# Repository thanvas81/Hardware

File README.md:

🚀 Embedded Systems & Electronics Design Portfolio

This repository is a collection of hardware, firmware, and PCB design projects I have built across the past year.
It is organized as a monorepo, where each folder represents a separate embedded-systems project, including Raspberry Pi HATs, sensor boards, analog filters, diagnostic tools, and custom control modules.

This portfolio is part of my application to the University of California, Berkeley, and showcases my experience in:

Embedded systems design

PCB layout & electronics hardware

Microcontroller programming

Signal processing

IoT sensors & digital interfaces

Electronics testing & validation

📁 Repository Structure

Each folder in this repository is a standalone hardware/firmware project.
Below is an index of the major projects:

📂 Full Project List

HAT_rpi/ – Raspberry Pi HAT with mixed-signal I/O.

bandpass_filter/ – Analog band-pass filter used for signal conditioning.

buzzer_door_detect_board/ – Door detection + buzzer notification circuit.

can_bus_extension_v2/ – CAN bus expansion board.

canlink/ – CAN communication module.

control-unit-v2-upper/ – Upper control unit for embedded system integration.

control_unit_tester/ – Bench-top electronics diagnostic/testing tool.

ds18b20_protection/ – Protection adapter for DS18B20 temperature sensors.

dummy_control_unit/ – Mock control unit for lab testing.

led-display/ – Custom LED display driver board.

lightsensor/ – Light-sensing analog front-end.

mini_upper_board_relay_analog/ – Compact control/relay board.

rfid_rpi_hat/ – RFID HAT for Raspberry Pi.

rgb_led/ – RGB LED driver circuit.

rpi-pico-diagnostic-tester/ – RP2040-based I/O diagnostic and logic-level tester.

serial_io_expander/ – Serial digital I/O expansion board.

switches_board/ – Switch interface board.

test/ – Miscellaneous test files.

tracker-master/ – Tracking/monitoring module.

upper-board-analog-inputs-and-relay/ – Analog input + relay control upper board.

upperboard_analog_relay_input/ – Relay + analog input interface board.

vehicle_io_validator/ – Automotive I/O validator.

(You can edit the descriptions later if you want more detail.)

🛠️ Technologies & Tools

Hardware Design

PCB design tools (KiCad)

Analog & digital circuit design

Embedded hardware validation

CAN, I2C, SPI, UART interfaces

C microcontroller firmware

Python (Raspberry Pi, testing scripts)

RP2040 (Raspberry Pi Pico)

Raspberry Pi OS

Testing Equipment

Oscilloscope

Logic analyzer

Multimeter & bench power supplies

📘 How to Explore

Each project folder may contain:

Schematics

PCB layouts

Documentation

You can browse any project individually by opening its folder.

🎯 Purpose of This Repository

This monorepo serves as a technical portfolio demonstrating my practical experience with embedded systems, electronics engineering, and real-world hardware development.
I hope it provides a clear view of my engineering interests and capabilities.

📬 Contact

If you have any questions or want to discuss these projects, feel free to reach out:

Athanasios Vasiloglou
th.vasiloglou81@gmail.com

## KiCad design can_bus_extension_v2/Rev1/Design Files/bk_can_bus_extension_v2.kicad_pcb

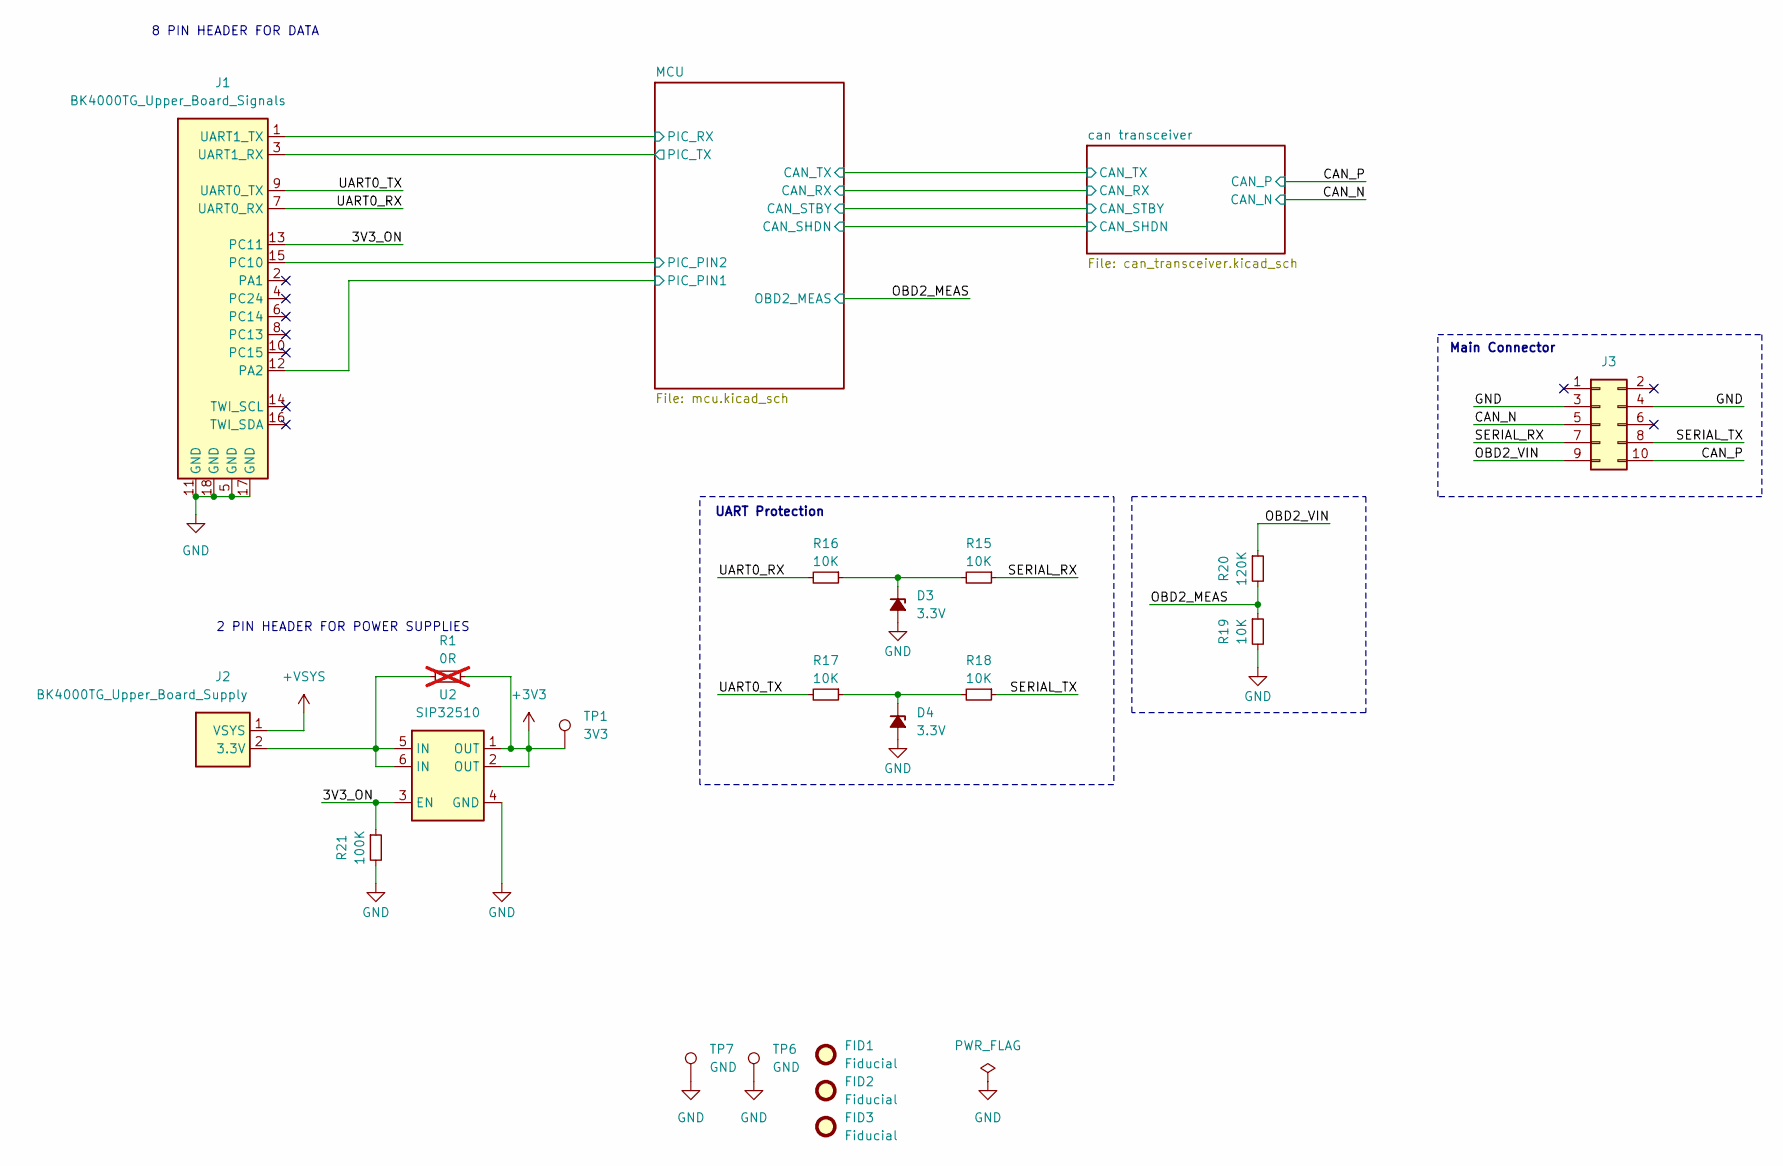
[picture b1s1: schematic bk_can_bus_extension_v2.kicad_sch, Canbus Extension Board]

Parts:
D3, D4: 3.3V; D_SOD-123
FID1, FID2, FID3: Fiducial; Fiducial_1mm_Mask2mm
J1: BK4000TG_Upper_Board_Signals; PinSocket_2x09_P2.54mm_Vertical
J2: BK4000TG_Upper_Board_Supply; PinSocket_1x02_P2.54mm_Vertical
J3: Conn_02x05_Odd_Even; Molex_Mini-Fit_Jr_5569-10A2_2x05_P4.20mm_Horizontal
R1: 0R; R_0805_2012Metric_Pad1.20x1.40mm_HandSolder; not fitted
R15, R16, R17, R18, R19: 10K; R_0603_1608Metric
R20: 120K; R_0603_1608Metric
R21: 100K; R_0603_1608Metric
TP1: 3V3; TestPoint_Pad_D2.0mm
TP6, TP7: GND; TestPoint_Pad_D2.0mm
U2: SIP32510; TSOT-23-6

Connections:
+3V3: R1.2, TP1.1, U2.1 (OUT), U2.2 (OUT); also elsewhere on the board
+VSYS: J2.1 (VSYS)
/3V3_ON: J1.13 (PC11), R21.1, U2.3 (EN)
/CAN_N: J3.5; also elsewhere on the board
/CAN_P: J3.10; also elsewhere on the board
/MCU/PIC_PIN1: J1.12 (PA2); also elsewhere on the board
/MCU/PIC_PIN2: J1.15 (PC10); also elsewhere on the board
/MCU/PIC_RX: J1.1 (UART1_TX); also elsewhere on the board
/MCU/PIC_TX: J1.3 (UART1_RX); also elsewhere on the board
/OBD2_MEAS: R19.1, R20.2; also elsewhere on the board
/OBD2_VIN: J3.9, R20.1
/SERIAL_RX: J3.7, R15.1
/SERIAL_TX: J3.8, R18.1
/UART0_RX: J1.7 (UART0_RX), R16.2
/UART0_TX: J1.9 (UART0_TX), R17.2
GND: D3.2 (A), D4.2 (A), J1.5 (GND), J1.11 (GND), J1.17 (GND), J1.18 (GND), J3.3, J3.4, R19.2, R21.2, TP6.1, TP7.1, U2.4 (GND); also elsewhere on the board
unnamed: D3.1 (K), R15.2, R16.1
unnamed: D4.1 (K), R17.1, R18.2
unnamed: J2.2 (3.3V), R1.1, U2.5 (IN), U2.6 (IN)

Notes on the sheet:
8 PIN HEADER FOR DATA
2 PIN HEADER FOR POWER SUPPLIES
Main Connector
UART Protection

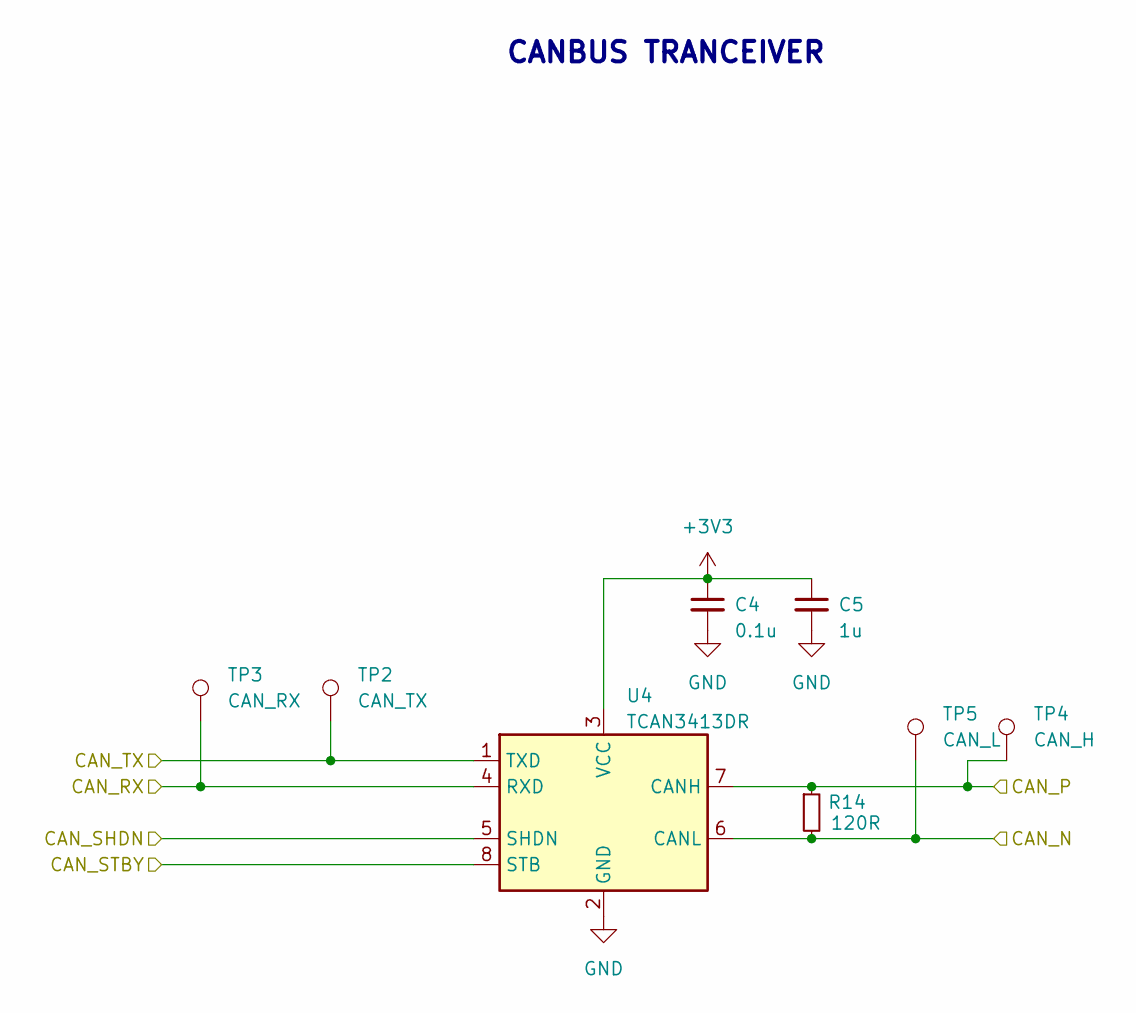
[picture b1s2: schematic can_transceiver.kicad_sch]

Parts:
C4: 0.1u; C_0603_1608Metric
C5: 1u; C_0603_1608Metric
R14: 120R; R_0805_2012Metric
TP2: CAN_TX; TestPoint_Pad_D2.0mm
TP3: CAN_RX; TestPoint_Pad_D2.0mm
TP4: CAN_H; TestPoint_Pad_D2.0mm
TP5: CAN_L; TestPoint_Pad_D2.0mm
U4: TCAN3413DR; SOIC-8_3.9x4.9mm_P1.27mm

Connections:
+3V3: C4.1, C5.1, U4.3 (VCC); also elsewhere on the board
/CAN_N: R14.2, TP5.1, U4.6 (CANL); also elsewhere on the board
/CAN_P: R14.1, TP4.1, U4.7 (CANH); also elsewhere on the board
/MCU/CAN_RX: TP3.1, U4.4 (RXD); also elsewhere on the board
/MCU/CAN_SHDN: U4.5 (SHDN); also elsewhere on the board
/MCU/CAN_STBY: U4.8 (STB); also elsewhere on the board
/MCU/CAN_TX: TP2.1, U4.1 (TXD); also elsewhere on the board
GND: C4.2, C5.2, U4.2 (GND); also elsewhere on the board

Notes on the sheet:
CANBUS TRANCEIVER

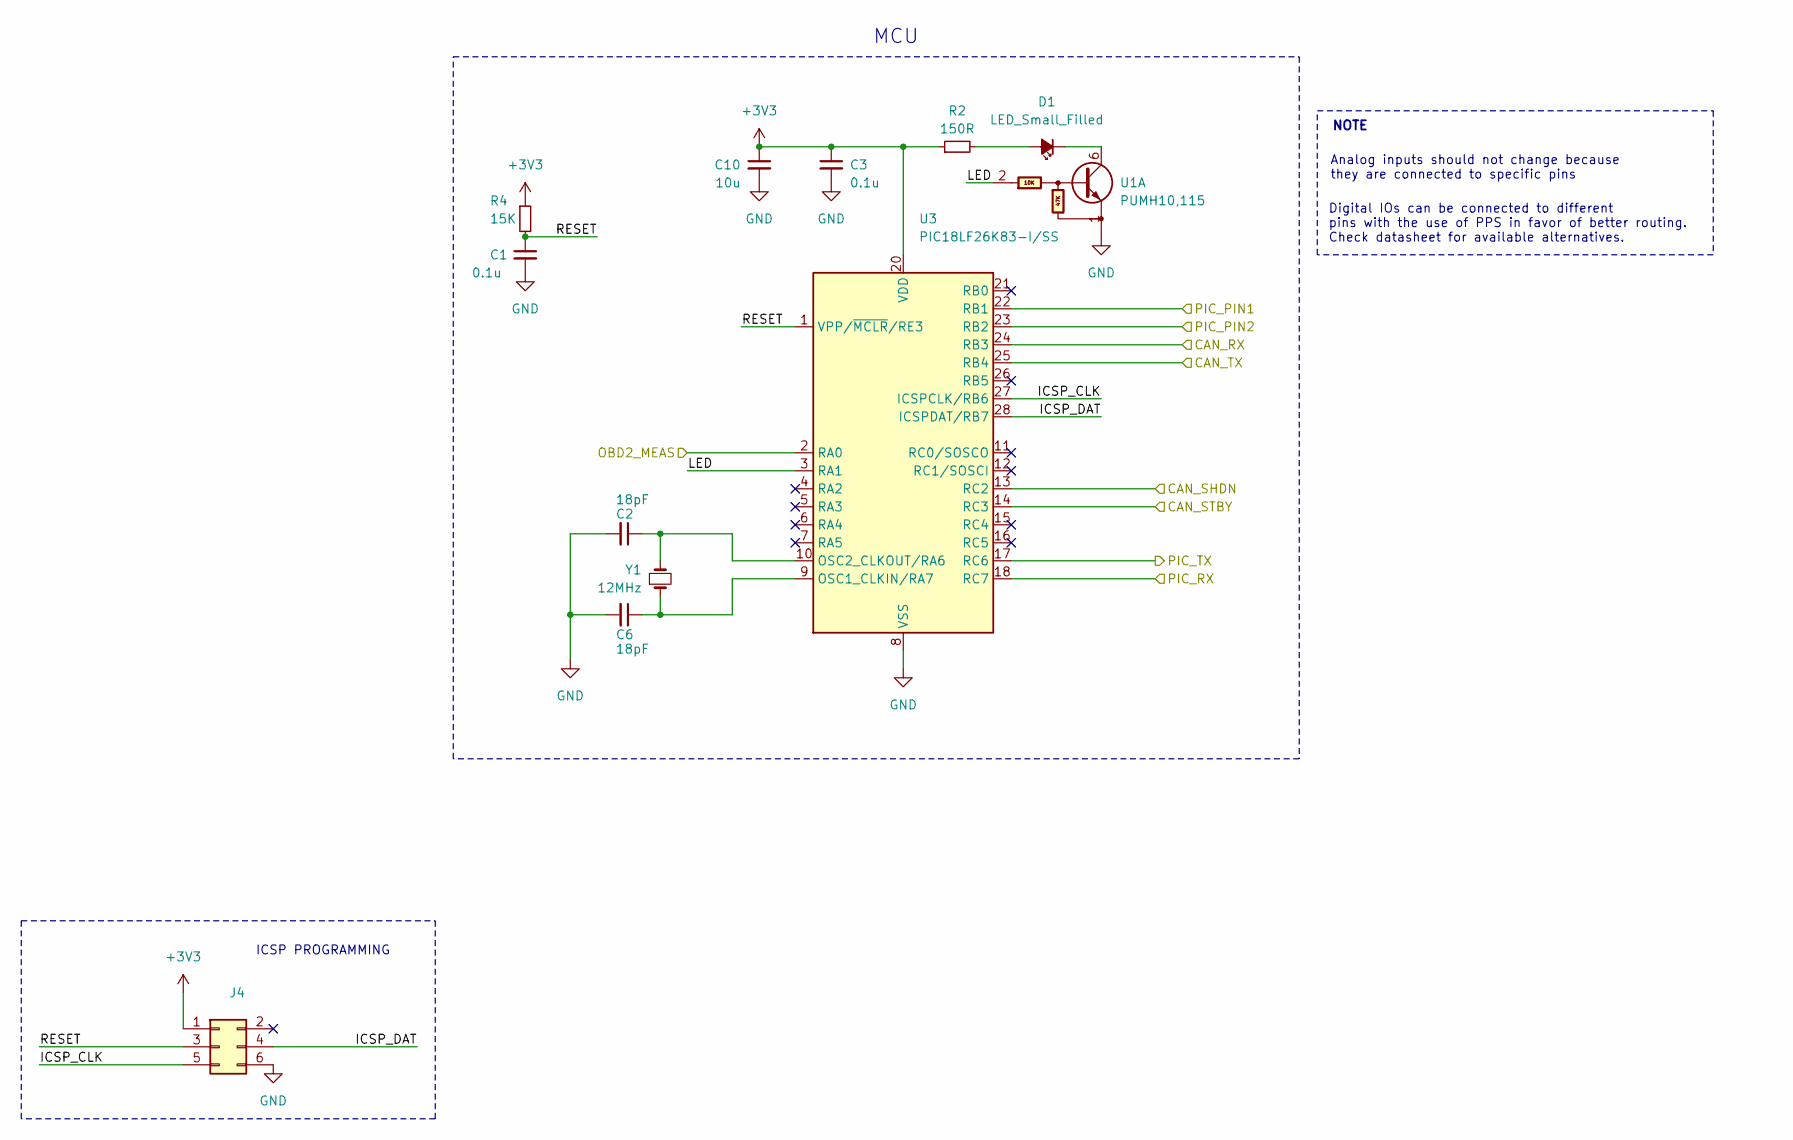
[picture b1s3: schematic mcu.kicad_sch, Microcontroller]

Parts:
C1, C3: 0.1u; C_0603_1608Metric
C2, C6: 18pF; C_0603_1608Metric
C10: 10u; C_0805_2012Metric
D1: LED_Small_Filled; LED_0603_1608Metric
J4: -; PinHeader_2x03_P2.54mm_Vertical
R2: 150R; R_0603_1608Metric
R4: 15K; R_0603_1608Metric
U1: PUMH10,115; SOT-363_SC-70-6
U3: PIC18LF26K83-I/SS; SSOP-28_5.3x10.2mm_P0.65mm
Y1: 12MHz; Crystal_SMD_5032-2Pin_5.0x3.2mm

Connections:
+3V3: C3.1, C10.1, J4.1, R2.1, R4.1, U3.20 (VDD); also elsewhere on the board
/MCU/CAN_RX: U3.24 (RB3); also elsewhere on the board
/MCU/CAN_SHDN: U3.13 (RC2); also elsewhere on the board
/MCU/CAN_STBY: U3.14 (RC3); also elsewhere on the board
/MCU/CAN_TX: U3.25 (RB4); also elsewhere on the board
/MCU/ICSP_CLK: J4.5, U3.27 (ICSPCLK/RB6)
/MCU/ICSP_DAT: J4.4, U3.28 (ICSPDAT/RB7)
/MCU/LED: U1.2, U3.3 (RA1)
/MCU/PIC_PIN1: U3.22 (RB1); also elsewhere on the board
/MCU/PIC_PIN2: U3.23 (RB2); also elsewhere on the board
/MCU/PIC_RX: U3.18 (RC7); also elsewhere on the board
/MCU/PIC_TX: U3.17 (RC6); also elsewhere on the board
/MCU/RESET: C1.1, J4.3, R4.2, U3.1 (VPP/~MCLR/RE3)
/OBD2_MEAS: U3.2 (RA0); also elsewhere on the board
GND: C1.2, C2.2, C3.2, C6.2, C10.2, J4.6, U1.1, U3.8 (VSS), U3.19 (VSS); also elsewhere on the board
unnamed: D1.2 (A), R2.2
unnamed: D1.1 (K), U1.6
unnamed: C6.1, U3.9 (OSC1_CLKIN/RA7), Y1.1
unnamed: C2.1, U3.10 (OSC2_CLKOUT/RA6), Y1.2

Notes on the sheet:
Digital IOs can be connected to different pins with the use of PPS in favor of better routing. Check datasheet for available alternatives.
NOTE
MCU
Analog inputs should not change because they are connected to specific pins
ICSP PROGRAMMING

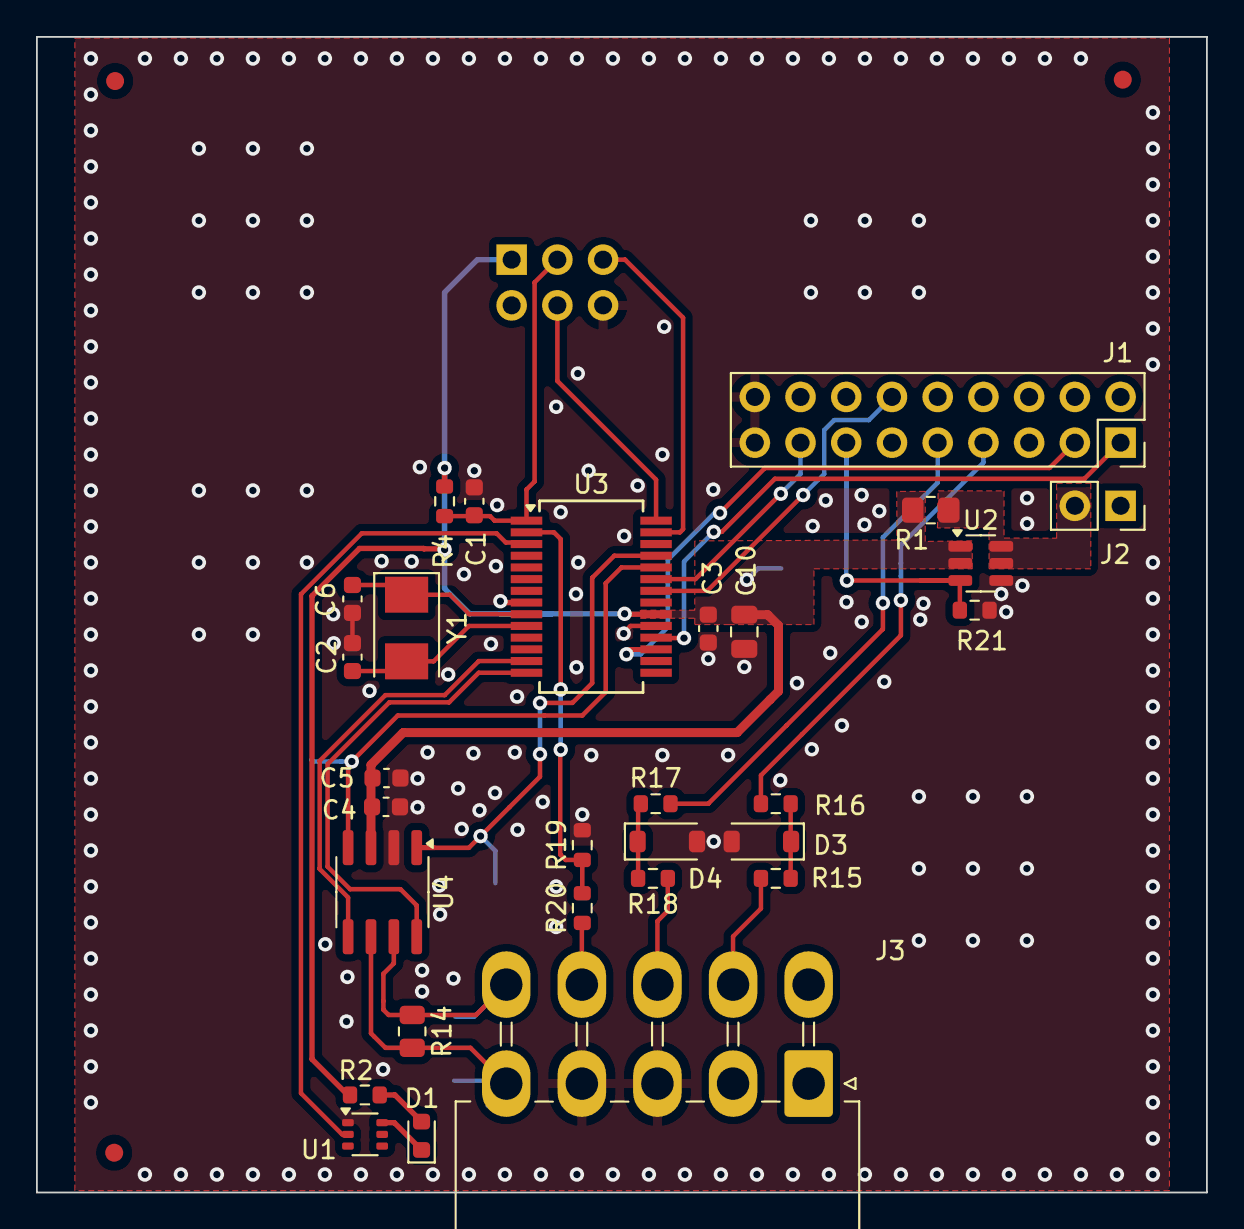
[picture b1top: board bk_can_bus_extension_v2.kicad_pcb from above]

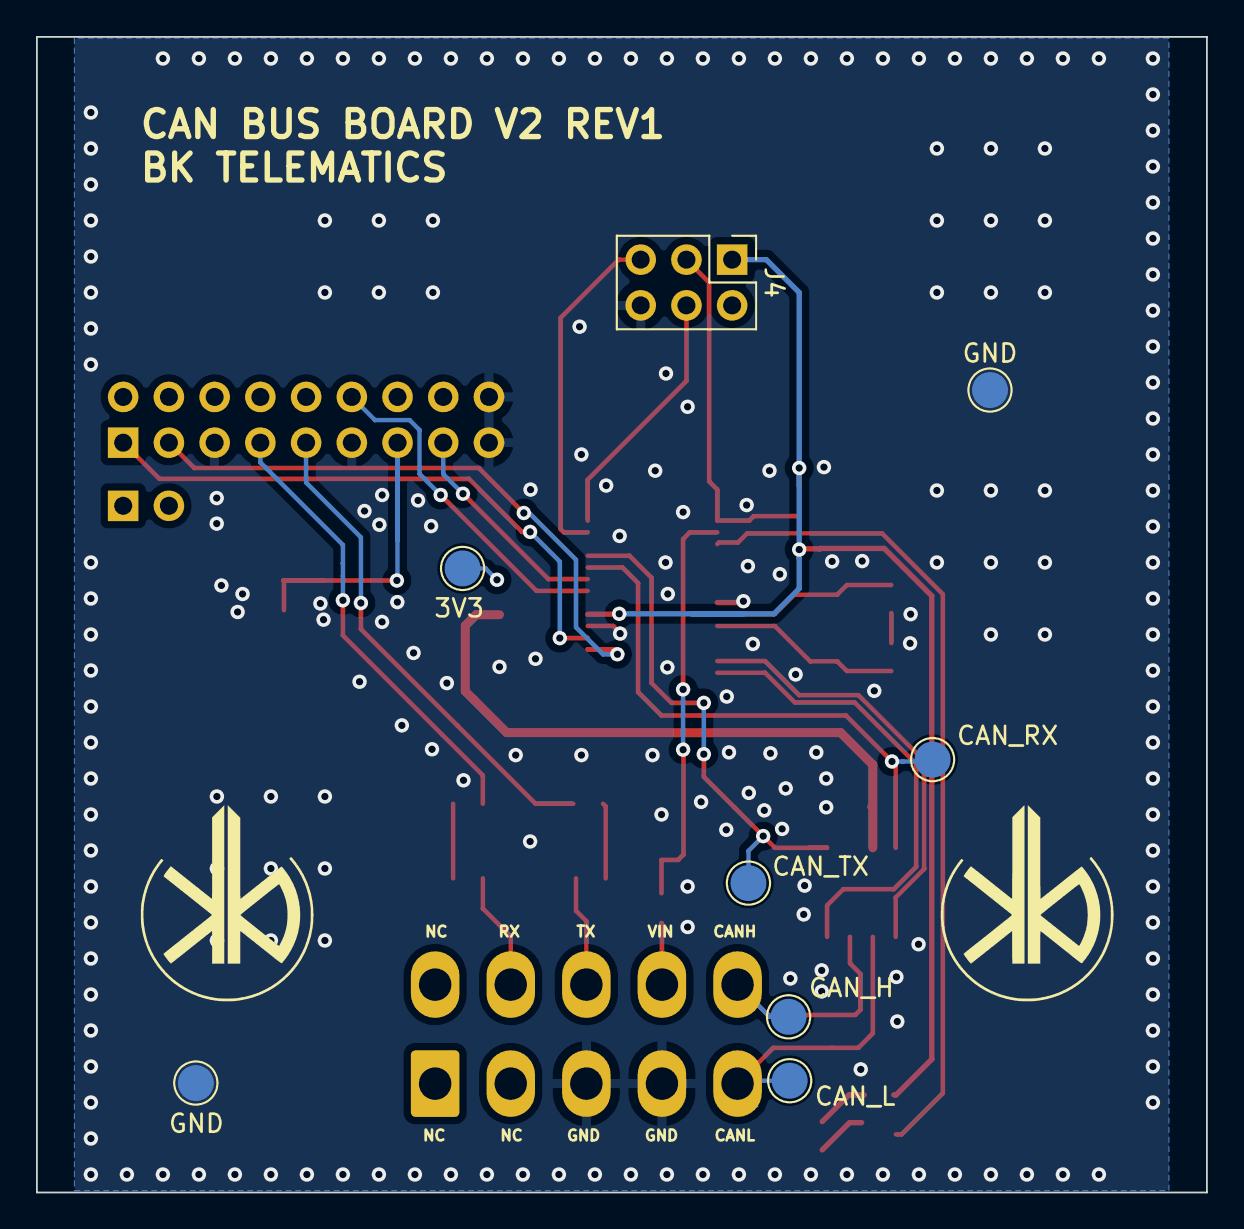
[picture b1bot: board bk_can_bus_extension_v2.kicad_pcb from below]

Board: 2 copper layers, 65.0 x 64.2 mm, 40 parts (8 on the bottom side), 30 nets.

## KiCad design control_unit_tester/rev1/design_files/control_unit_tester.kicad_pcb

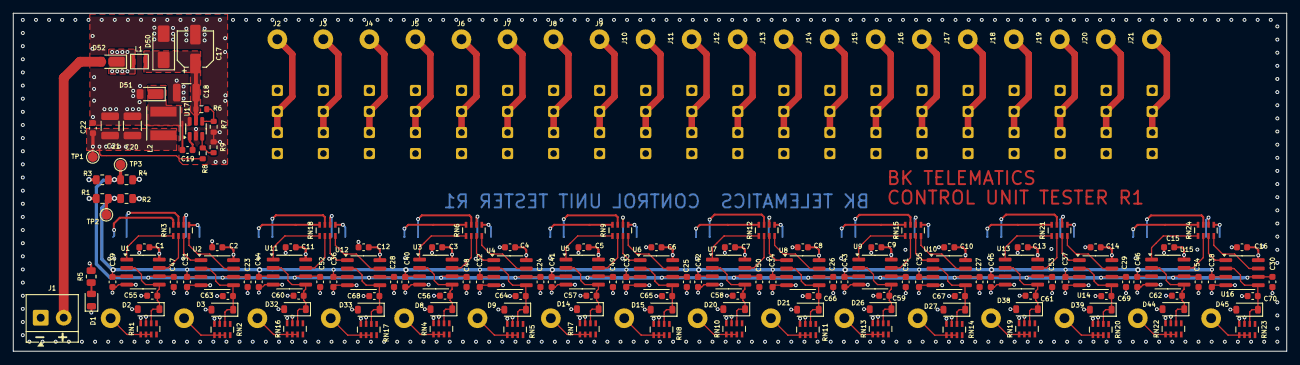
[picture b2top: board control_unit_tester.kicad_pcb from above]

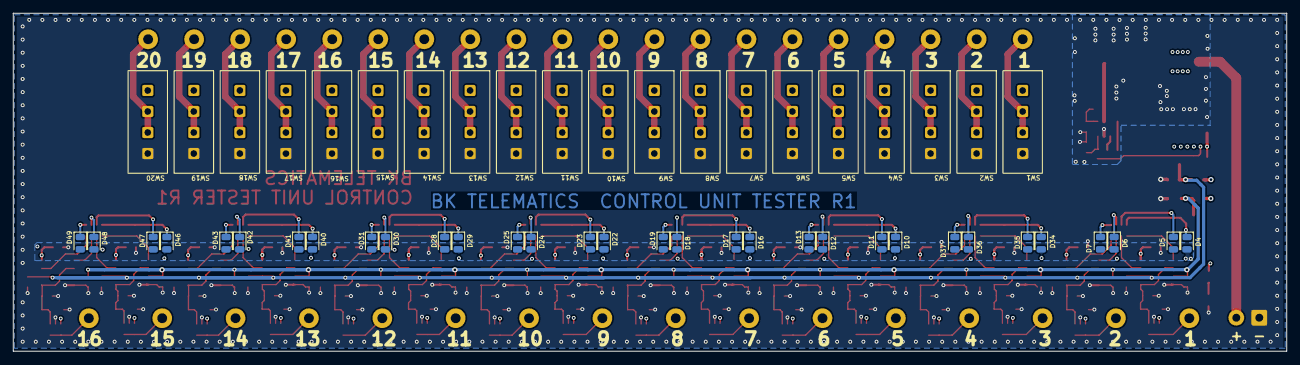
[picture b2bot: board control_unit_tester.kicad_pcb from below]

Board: 4 copper layers, 193.9 x 51.5 mm, 234 parts (52 on the bottom side), 128 nets.

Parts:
C1, C2, C3, C4, C5, C6, C7, C8, C9, C10, C11, C12, C13, C14, C15, C16, C19, C22, C23, C24, C25, C26, C27, C28, C29, C30, C31, C32, C33, C34, C35, C36, C37, C38, C39, C40, C41, C42, C43, C44, C45, C46, C47, C48, C49, C50, C51, C52, C53, C54, C55, C56, C57, C58, C59, C60, C61, C62, C63, C64, C65, C66, C67, C68, C69, C70: 0.1u; C_0603_1608Metric
C17: 10u; CP_Elec_5x5.3
C18: 2.2u; C_1210_3225Metric
C20, C21: 22u; C_1210_3225Metric
D1: LED 0805 SMD; LED_0805_2012Metric
D2, D3, D8, D9, D14, D15, D20, D21, D26, D27, D32, D33, D38, D39, D44, D45: 4.7V; D_SOD-123
D4, D5, D6, D7, D10, D11, D12, D13, D16, D17, D18, D19, D22, D23, D24, D25, D28, D29, D30, D31, D34, D35, D36, D37, D40, D41, D42, D43, D46, D47, D48, D49: LED; LED_0805_2012Metric
D50: SMAJ40CAe3/TR13; D_SMA
D51, D52: SBR3U60P1Q-7; D_PowerDI-123
J1: Conn_01x02; TerminalBlock_4Ucon_1x02_P3.50mm_Horizontal
J2, J3, J4, J5, J6, J7, J8, J9, J10, J11, J12, J13, J14, J15, J16, J17, J18, J19, J20, J21, J22, J23, J24, J25, J26, J27, J28, J29, J30, J31, J32, J33, J34, J35, J36, J37: T.H. Pad; Hole_pad_1.5x3_round
L1: 4.7uH; L_TDK_VLS252012HBX
L2: 22uH; L_Taiyo-Yuden_NR-50xx
R1, R4: 20Κ; R_0805_2012Metric
R2, R3: 80Κ; R_0805_2012Metric
R5: 470R; R_0805_2012Metric
R6, R7: 100K; R_0603_1608Metric
R8: 54.9K; R_0603_1608Metric
R9: 10K; R_0603_1608Metric
RN1, RN2, RN4, RN5, RN7, RN8, RN10, RN11, RN13, RN14, RN16, RN17, RN19, RN20, RN22, RN23: 1K; R_Array_Concave_4x0603
RN3, RN6, RN9, RN12, RN15, RN18, RN21, RN24: 470R; R_Array_Concave_4x0603
SW1, SW2, SW3, SW4, SW5, SW6, SW7, SW8, SW9, SW10, SW11, SW12, SW13, SW14, SW15, SW16, SW17, SW18, SW19, SW20: SLW-156646-5A-N-D
TP1, TP2, TP3: TestPoint; TestPoint_Pad_D1.5mm
U1, U2, U3, U4, U5, U6, U7, U8, U9, U10, U11, U12, U13, U14, U15, U16: AZV3002S-13; SOIC-8_3.9x4.9mm_P1.27mm
U17: LV2862x; SOT-23-6

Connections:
+5V: C1.1, C2.1, C3.1, C4.1, C5.1, C6.1, C7.1, C8.1, C9.1, C10.1, C11.1, C12.1, C13.1, C14.1, C15.1, C16.1, C20.1, C21.1, C22.1, D4.2 (A), D5.2 (A), D6.2 (A), D7.2 (A), D10.2 (A), D11.2 (A), D12.2 (A), D13.2 (A), D16.2 (A), D17.2 (A), D18.2 (A), D19.2 (A), D22.2 (A), D23.2 (A), D24.2 (A), D25.2 (A), D28.2 (A), D29.2 (A), D30.2 (A), D31.2 (A), D34.2 (A), D35.2 (A), D36.2 (A), D37.2 (A), D40.2 (A), D41.2 (A), D42.2 (A), D43.2 (A), D46.2 (A), D47.2 (A), D48.2 (A), D49.2 (A), L2.2, R1.1, R3.1, R5.2, R8.2, RN1.8 (R1.2), RN2.4 (R4.1), RN4.8 (R1.2), RN5.4 (R4.1), RN7.8 (R1.2), RN8.4 (R4.1), RN10.8 (R1.2), RN11.4 (R4.1), RN13.8 (R1.2), RN14.4 (R4.1), RN16.8 (R1.2), RN17.4 (R4.1), RN19.8 (R1.2), RN20.4 (R4.1), RN22.8 (R1.2), RN23.4 (R4.1), TP1.1, U1.8 (V+), U2.8 (V+), U3.8 (V+), U4.8 (V+), U5.8 (V+), U6.8 (V+), U7.8 (V+), U8.8 (V+), U9.8 (V+), U10.8 (V+), U11.8 (V+), U12.8 (V+), U13.8 (V+), U14.8 (V+), U15.8 (V+), U16.8 (V+)
+VIN: D52.1 (K), L1.1, SW1.1, SW2.1, SW3.1, SW4.1, SW5.1, SW6.1, SW7.1, SW8.1, SW9.1, SW10.1, SW11.1, SW12.1, SW13.1, SW14.1, SW15.1, SW16.1, SW17.1, SW18.1, SW19.1, SW20.1
/IN1: J22.1, RN1.1 (R1.1), RN1.2 (R2.1), RN1.3 (R3.1)
/IN2: J23.1, RN2.5 (R4.2), RN2.6 (R3.2), RN2.7 (R2.2)
/IN3: J26.1, RN4.1 (R1.1), RN4.2 (R2.1), RN4.3 (R3.1)
/IN4: J27.1, RN5.5 (R4.2), RN5.6 (R3.2), RN5.7 (R2.2)
/IN5: J28.1, RN7.1 (R1.1), RN7.2 (R2.1), RN7.3 (R3.1)
/IN6: J29.1, RN8.5 (R4.2), RN8.6 (R3.2), RN8.7 (R2.2)
/IN7: J30.1, RN10.1 (R1.1), RN10.2 (R2.1), RN10.3 (R3.1)
/IN8: J31.1, RN11.5 (R4.2), RN11.6 (R3.2), RN11.7 (R2.2)
/IN9: J32.1, RN13.1 (R1.1), RN13.2 (R2.1), RN13.3 (R3.1)
/IN10: J33.1, RN14.5 (R4.2), RN14.6 (R3.2), RN14.7 (R2.2)
/IN11: J24.1, RN16.1 (R1.1), RN16.2 (R2.1), RN16.3 (R3.1)
/IN12: J25.1, RN17.5 (R4.2), RN17.6 (R3.2), RN17.7 (R2.2)
/IN13: J34.1, RN19.1 (R1.1), RN19.2 (R2.1), RN19.3 (R3.1)
/IN14: J35.1, RN20.5 (R4.2), RN20.6 (R3.2), RN20.7 (R2.2)
/IN15: J36.1, RN22.1 (R1.1), RN22.2 (R2.1), RN22.3 (R3.1)
/IN16: J37.1, RN23.5 (R4.2), RN23.6 (R3.2), RN23.7 (R2.2)
/OUT1: J2.1, SW1.2, SW1.3
/OUT2: J3.1, SW2.2, SW2.3
/OUT3: J4.1, SW3.2, SW3.3
/OUT4: J5.1, SW4.2, SW4.3
/OUT5: J6.1, SW5.2, SW5.3
/OUT6: J7.1, SW6.2, SW6.3
/OUT7: J8.1, SW7.2, SW7.3
/OUT8: J9.1, SW8.2, SW8.3
/OUT9: J10.1, SW9.2, SW9.3
/OUT10: J11.1, SW10.2, SW10.3
/OUT11: J12.1, SW11.2, SW11.3
/OUT12: J13.1, SW12.2, SW12.3
/OUT13: J14.1, SW13.2, SW13.3
/OUT14: J15.1, SW14.2, SW14.3
/OUT15: J16.1, SW15.2, SW15.3
/OUT16: J17.1, SW16.2, SW16.3
/OUT17: J18.1, SW17.2, SW17.3
/OUT18: J19.1, SW18.2, SW18.3
/OUT19: J20.1, SW19.2, SW19.3
/OUT20: J21.1, SW20.2, SW20.3
/VREF_HIGH: C31.1, C32.1, C33.1, C34.1, C35.1, C36.1, C37.1, C38.1, C39.1, C40.1, C41.1, C42.1, C43.1, C44.1, C45.1, C46.1, R1.2, R2.1, TP2.1, U1.3 (+), U2.3 (+), U3.3 (+), U4.3 (+), U5.3 (+), U6.3 (+), U7.3 (+), U8.3 (+), U9.3 (+), U10.3 (+), U11.3 (+), U12.3 (+), U13.3 (+), U14.3 (+), U15.3 (+), U16.3 (+)
/VREF_LOW: C23.1, C24.1, C25.1, C26.1, C27.1, C28.1, C29.1, C30.1, C47.1, C48.1, C49.1, C50.1, C51.1, C52.1, C53.1, C54.1, R3.2, R4.1, TP3.1, U1.6 (-), U2.6 (-), U3.6 (-), U4.6 (-), U5.6 (-), U6.6 (-), U7.6 (-), U8.6 (-), U9.6 (-), U10.6 (-), U11.6 (-), U12.6 (-), U13.6 (-), U14.6 (-), U15.6 (-), U16.6 (-)
/power supply/+VIN_PROTECTED: C17.1, C18.1, D50.1 (K), L1.2, R6.2, U17.5 (VIN)
/power supply/SW: C19.2, D51.1 (K), L2.1, U17.6 (SW)
GND: C1.2, C2.2, C3.2, C4.2, C5.2, C6.2, C7.2, C8.2, C9.2, C10.2, C11.2, C12.2, C13.2, C14.2, C15.2, C16.2, C17.2, C18.2, C20.2, C21.2, C22.2, C23.2, C24.2, C25.2, C26.2, C27.2, C28.2, C29.2, C30.2, C31.2, C32.2, C33.2, C34.2, C35.2, C36.2, C37.2, C38.2, C39.2, C40.2, C41.2, C42.2, C43.2, C44.2, C45.2, C46.2, C47.2, C48.2, C49.2, C50.2, C51.2, C52.2, C53.2, C54.2, C55.2, C56.2, C57.2, C58.2, C59.2, C60.2, C61.2, C62.2, C63.2, C64.2, C65.2, C66.2, C67.2, C68.2, C69.2, C70.2, D1.1 (K), D2.2 (A), D3.2 (A), D8.2 (A), D9.2 (A), D14.2 (A), D15.2 (A), D20.2 (A), D21.2 (A), D26.2 (A), D27.2 (A), D32.2 (A), D33.2 (A), D38.2 (A), D39.2 (A), D44.2 (A), D45.2 (A), D50.2 (A), D51.2 (A), J1.1, R2.2, R4.2, R7.1, R9.1, RN1.7 (R2.2), RN2.3 (R3.1), RN4.7 (R2.2), RN5.3 (R3.1), RN7.7 (R2.2), RN8.3 (R3.1), RN10.7 (R2.2), RN11.3 (R3.1), RN13.7 (R2.2), RN14.3 (R3.1), RN16.7 (R2.2), RN17.3 (R3.1), RN19.7 (R2.2), RN20.3 (R3.1), RN22.7 (R2.2), RN23.3 (R3.1), SW1.4, SW2.4, SW3.4, SW4.4, SW5.4, SW6.4, SW7.4, SW8.4, SW9.4, SW10.4, SW11.4, SW12.4, SW13.4, SW14.4, SW15.4, SW16.4, SW17.4, SW18.4, SW19.4, SW20.4, U1.4 (V-), U2.4 (V-), U3.4 (V-), U4.4 (V-), U5.4 (V-), U6.4 (V-), U7.4 (V-), U8.4 (V-), U9.4 (V-), U10.4 (V-), U11.4 (V-), U12.4 (V-), U13.4 (V-), U14.4 (V-), U15.4 (V-), U16.4 (V-), U17.2 (GND)
unnamed: D1.2 (A), R5.1
unnamed: C55.1, D2.1 (K), RN1.6 (R3.2), U1.2 (-), U1.5 (+)
unnamed: C63.1, D3.1 (K), RN2.2 (R2.1), U2.2 (-), U2.5 (+)
unnamed: D4.1 (K), RN3.8 (R1.2)
unnamed: D5.1 (K), RN3.7 (R2.2)
unnamed: D6.1 (K), RN3.6 (R3.2)
unnamed: D7.1 (K), RN3.5 (R4.2)
unnamed: C56.1, D8.1 (K), RN4.6 (R3.2), U3.2 (-), U3.5 (+)
unnamed: C64.1, D9.1 (K), RN5.2 (R2.1), U4.2 (-), U4.5 (+)
unnamed: D10.1 (K), RN6.8 (R1.2)
unnamed: D11.1 (K), RN6.7 (R2.2)
unnamed: D12.1 (K), RN6.6 (R3.2)
unnamed: D13.1 (K), RN6.5 (R4.2)
unnamed: C57.1, D14.1 (K), RN7.6 (R3.2), U5.2 (-), U5.5 (+)
unnamed: C65.1, D15.1 (K), RN8.2 (R2.1), U6.2 (-), U6.5 (+)
unnamed: D16.1 (K), RN9.8 (R1.2)
unnamed: D17.1 (K), RN9.7 (R2.2)
unnamed: D18.1 (K), RN9.6 (R3.2)
unnamed: D19.1 (K), RN9.5 (R4.2)
unnamed: C58.1, D20.1 (K), RN10.6 (R3.2), U7.2 (-), U7.5 (+)
unnamed: C66.1, D21.1 (K), RN11.2 (R2.1), U8.2 (-), U8.5 (+)
unnamed: D22.1 (K), RN12.8 (R1.2)
unnamed: D23.1 (K), RN12.7 (R2.2)
unnamed: D24.1 (K), RN12.6 (R3.2)
unnamed: D25.1 (K), RN12.5 (R4.2)
unnamed: C59.1, D26.1 (K), RN13.6 (R3.2), U9.2 (-), U9.5 (+)
unnamed: C67.1, D27.1 (K), RN14.2 (R2.1), U10.2 (-), U10.5 (+)
unnamed: D28.1 (K), RN15.8 (R1.2)
unnamed: D29.1 (K), RN15.7 (R2.2)
unnamed: D30.1 (K), RN15.6 (R3.2)
unnamed: D31.1 (K), RN15.5 (R4.2)
unnamed: C60.1, D32.1 (K), RN16.6 (R3.2), U11.2 (-), U11.5 (+)
unnamed: C68.1, D33.1 (K), RN17.2 (R2.1), U12.2 (-), U12.5 (+)
unnamed: D34.1 (K), RN18.8 (R1.2)
unnamed: D35.1 (K), RN18.7 (R2.2)
unnamed: D36.1 (K), RN18.6 (R3.2)
unnamed: D37.1 (K), RN18.5 (R4.2)
unnamed: C61.1, D38.1 (K), RN19.6 (R3.2), U13.2 (-), U13.5 (+)
unnamed: C69.1, D39.1 (K), RN20.2 (R2.1), U14.2 (-), U14.5 (+)
unnamed: D40.1 (K), RN21.8 (R1.2)
unnamed: D41.1 (K), RN21.7 (R2.2)
unnamed: D42.1 (K), RN21.6 (R3.2)
unnamed: D43.1 (K), RN21.5 (R4.2)
unnamed: C62.1, D44.1 (K), RN22.6 (R3.2), U15.2 (-), U15.5 (+)
unnamed: C70.1, D45.1 (K), RN23.2 (R2.1), U16.2 (-), U16.5 (+)
unnamed: D46.1 (K), RN24.8 (R1.2)
unnamed: D47.1 (K), RN24.7 (R2.2)
unnamed: D48.1 (K), RN24.6 (R3.2)
unnamed: D49.1 (K), RN24.5 (R4.2)
unnamed: D52.2 (A), J1.2
unnamed: RN3.1 (R1.1), U1.1
unnamed: RN3.2 (R2.1), U1.7
unnamed: RN3.3 (R3.1), U2.1
unnamed: RN3.4 (R4.1), U2.7
unnamed: RN6.1 (R1.1), U3.1
unnamed: RN6.2 (R2.1), U3.7
unnamed: RN6.3 (R3.1), U4.1
unnamed: RN6.4 (R4.1), U4.7
unnamed: RN9.1 (R1.1), U5.1
unnamed: RN9.2 (R2.1), U5.7
unnamed: RN9.3 (R3.1), U6.1
unnamed: RN9.4 (R4.1), U6.7
unnamed: RN12.1 (R1.1), U7.1
unnamed: RN12.2 (R2.1), U7.7
unnamed: RN12.3 (R3.1), U8.1
unnamed: RN12.4 (R4.1), U8.7
unnamed: RN15.1 (R1.1), U9.1
unnamed: RN15.2 (R2.1), U9.7
unnamed: RN15.3 (R3.1), U10.1
unnamed: RN15.4 (R4.1), U10.7
unnamed: RN18.1 (R1.1), U11.1
unnamed: RN18.2 (R2.1), U11.7
unnamed: RN18.3 (R3.1), U12.1
unnamed: RN18.4 (R4.1), U12.7
unnamed: RN21.1 (R1.1), U13.1
unnamed: RN21.2 (R2.1), U13.7
unnamed: RN21.3 (R3.1), U14.1
unnamed: RN21.4 (R4.1), U14.7
unnamed: RN24.1 (R1.1), U15.1
unnamed: RN24.2 (R2.1), U15.7
unnamed: RN24.3 (R3.1), U16.1
unnamed: RN24.4 (R4.1), U16.7
unnamed: C19.1, U17.1 (CB)
unnamed: R8.1, R9.2, U17.3 (FB)
unnamed: R6.1, R7.2, U17.4 (~SHDN)

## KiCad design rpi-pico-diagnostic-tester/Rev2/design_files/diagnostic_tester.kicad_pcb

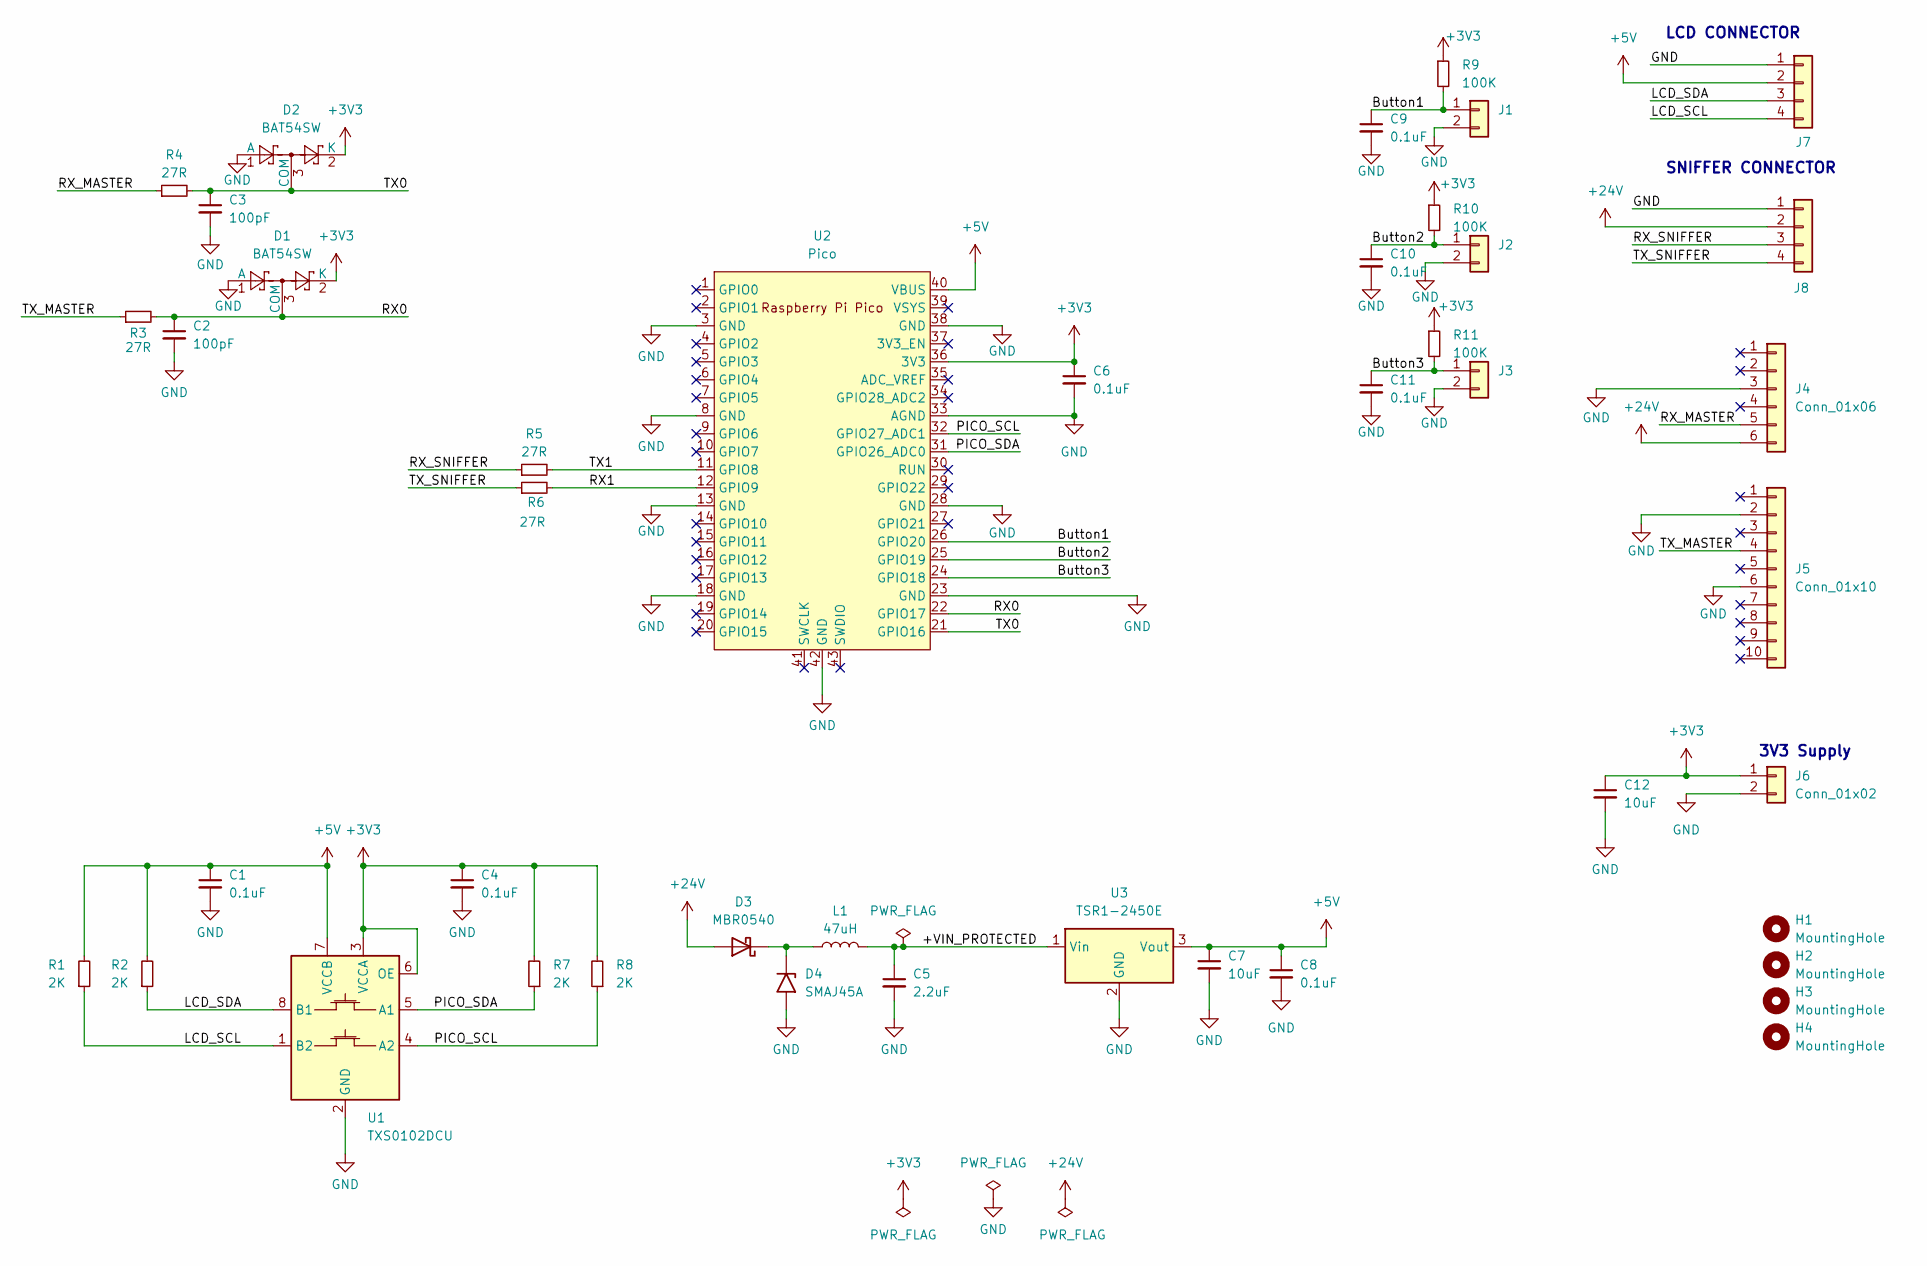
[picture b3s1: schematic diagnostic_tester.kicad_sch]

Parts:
C1, C4, C6, C8: 0.1uF; C_0603_1608Metric
C2, C3: 100pF; C_0603_1608Metric
C5: 2.2uF; C_1210_3225Metric
C7, C12: 10uF; C_0805_2012Metric
C9, C10, C11: 0.1uF; C_0805_2012Metric
D1, D2: BAT54SW; SOT-23-3
D3: MBR0540; D_SOD-123
D4: SMAJ45A; D_SMA
H1, H2, H3, H4: MountingHole; MountingHole_3.2mm_M3_ISO14580
J1, J2, J3, J6: Conn_01x02; PinHeader_1x02_P2.54mm_Vertical
J4: Conn_01x06; Molex_Mini-Fit_Jr_5569-06A2_2x03_P4.20mm_Horizontal
J5: Conn_01x10; Molex_Mini-Fit_Jr_5569-10A2_2x05_P4.20mm_Horizontal
J7, J8: Conn_01x04; PinHeader_1x04_P2.54mm_Vertical
L1: 47uH; L_Bourns_SRN6045TA
R1, R2, R7, R8: 2K; R_0603_1608Metric
R3, R4, R5, R6: 27R; R_0603_1608Metric
R9, R10, R11: 100K; R_0603_1608Metric
U1: TXS0102DCU; Package_SO_VSSOP-8_P0.5mm
U2: Pico; RPi_Pico_SMD_TH
U3: TSR1-2450E; Converter_DCDC_TRACO_TSR1-xxxxE_THT

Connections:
+3V3: C4.1, C6.1, C12.1, D1.2 (K), D2.2 (K), J6.1, R7.2, R8.2, R9.1, R10.1, R11.1, U1.3 (VCCA), U1.6 (OE), U2.36 (3V3)
+5V: C1.1, C7.1, C8.1, J7.2, R1.2, R2.2, U1.7 (VCCB), U2.40 (VBUS), U3.3 (Vout)
+24V: D3.2 (A), J4.6, J8.2
/+VIN_PROTECTED: C5.1, L1.2, U3.1 (Vin)
/Button1: C9.1, J1.1, R9.2, U2.26 (GPIO20)
/Button2: C10.1, J2.1, R10.2, U2.25 (GPIO19)
/Button3: C11.1, J3.1, R11.2, U2.24 (GPIO18)
/LCD_SCL: J7.4, R1.1, U1.1 (B2)
/LCD_SDA: J7.3, R2.1, U1.8 (B1)
/PICO_SCL: R8.1, U1.4 (A2), U2.32 (GPIO27_ADC1)
/PICO_SDA: R7.1, U1.5 (A1), U2.31 (GPIO26_ADC0)
/RX0: C2.1, D1.3 (COM), R3.2, U2.22 (GPIO17)
/RX1: R6.2, U2.12 (GPIO9)
/RX_MASTER: J4.5, R4.1
/RX_SNIFFER: J8.3, R5.1
/TX0: C3.1, D2.3 (COM), R4.2, U2.21 (GPIO16)
/TX1: R5.2, U2.11 (GPIO8)
/TX_MASTER: J5.4, R3.1
/TX_SNIFFER: J8.4, R6.1
GND: C1.2, C2.2, C3.2, C4.2, C5.2, C6.2, C7.2, C8.2, C9.2, C10.2, C11.2, C12.2, D1.1 (A), D2.1 (A), D4.2 (A2), J1.2, J2.2, J3.2, J4.3, J5.2, J5.6, J6.2, J7.1, J8.1, U1.2 (GND), U2.3 (GND), U2.8 (GND), U2.13 (GND), U2.18 (GND), U2.23 (GND), U2.28 (GND), U2.33 (AGND), U2.38 (GND), U2.42 (GND), U3.2 (GND)
unnamed: D3.1 (K), D4.1 (A1), L1.1

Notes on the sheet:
3V3 Supply
SNIFFER CONNECTOR
LCD CONNECTOR
